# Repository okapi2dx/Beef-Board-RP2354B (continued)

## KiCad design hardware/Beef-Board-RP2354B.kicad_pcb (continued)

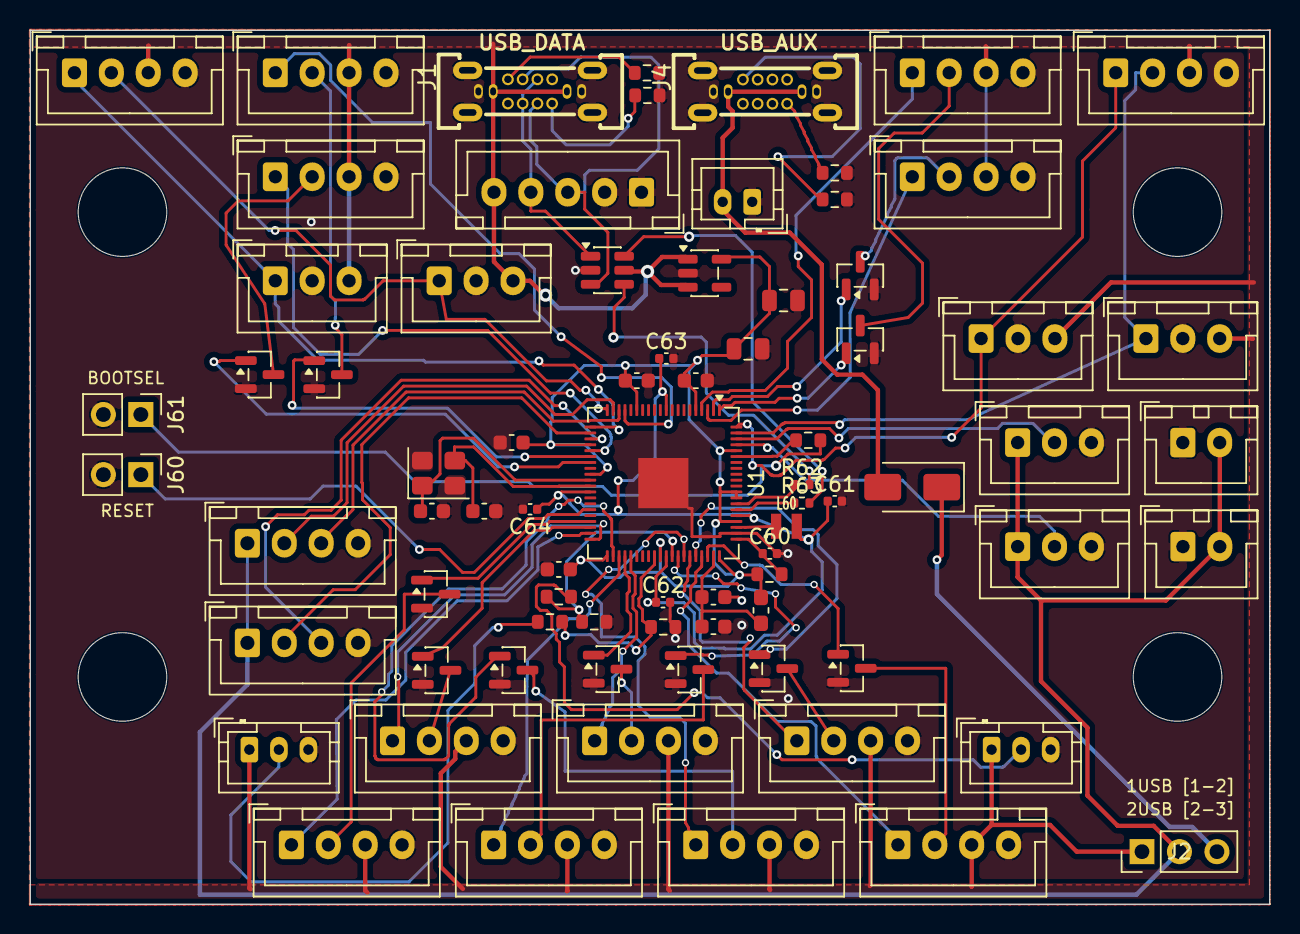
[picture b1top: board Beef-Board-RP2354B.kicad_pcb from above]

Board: 2 copper layers, 84.0 x 59.2 mm, 81 parts (0 on the bottom side), 72 nets.

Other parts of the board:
H1, H2, H3, H4: 6mm; MountingHole_6mm

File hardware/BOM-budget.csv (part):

Reference,Description/value,Qty,Footprint,Mounting,Suggested MPN (uncommitted),Manufacturer,LCSC SKU,Unit USD low,Unit USD high,Extended USD low,Extended USD high,Notes
C10,15pF,1,Capacitor_SMD:C_0603_1608Metric,SMT,0603 C0G/NP0 capacitor (candidate),Asian brands,,0.0050,0.0200,0.0050,0.0200,Capacitance per Value; voltage/tolerance not specified
C11,15pF,1,Capacitor_SMD:C_0603_1608Metric,SMT,0603 C0G/NP0 capacitor (candidate),Asian brands,,0.0050,0.0200,0.0050,0.0200,Capacitance per Value; voltage/tolerance not specified
C2,10uF,1,Capacitor_SMD:C_0805_2012Metric,SMT,0805 X5R/X7R capacitor (candidate),Asian brands,,0.0300,0.1000,0.0300,0.1000,10 uF; verify rated voltage and DC-bias derating
C3,4.7uF,1,Capacitor_SMD:C_0805_2012Metric,SMT,0805 X5R/X7R capacitor (candidate),Asian brands,,0.0200,0.0500,0.0200,0.0500,4.7 uF; verify rated voltage and DC-bias derating
C4,100nF,1,Capacitor_SMD:C_0603_1608Metric,SMT,"ceramic capacitor, X7R (candidate)",Asian brands,,0.0030,0.0150,0.0030,0.0150,Capacitance per Value; voltage/tolerance not specified
C5,100nF,1,Capacitor_SMD:C_0603_1608Metric,SMT,"ceramic capacitor, X7R (candidate)",Asian brands,,0.0030,0.0150,0.0030,0.0150,Capacitance per Value; voltage/tolerance not specified
C6,100nF,1,Capacitor_SMD:C_0603_1608Metric,SMT,"ceramic capacitor, X7R (candidate)",Asian brands,,0.0030,0.0150,0.0030,0.0150,Capacitance per Value; voltage/tolerance not specified
C60,4.7uF,1,Capacitor_SMD:C_0402_1005Metric,SMT,0402 X5R/X7R capacitor (candidate),Asian brands,,0.0100,0.0400,0.0100,0.0400,4.7 uF; verify rated voltage and DC-bias derating
C61,4.7uF,1,Capacitor_SMD:C_0402_1005Metric,SMT,0402 X5R/X7R capacitor (candidate),Asian brands,,0.0100,0.0400,0.0100,0.0400,4.7 uF; verify rated voltage and DC-bias derating
C62,100nF,1,Capacitor_SMD:C_0402_1005Metric,SMT,"ceramic capacitor, X7R (candidate)",Asian brands,,0.0030,0.0150,0.0030,0.0150,Capacitance per Value; voltage/tolerance not specified
C63,100nF,1,Capacitor_SMD:C_0402_1005Metric,SMT,"ceramic capacitor, X7R (candidate)",Asian brands,,0.0030,0.0150,0.0030,0.0150,Capacitance per Value; voltage/tolerance not specified
C64,100nF,1,Capacitor_SMD:C_0402_1005Metric,SMT,"ceramic capacitor, X7R (candidate)",Asian brands,,0.0030,0.0150,0.0030,0.0150,Capacitance per Value; voltage/tolerance not specified
C7,100nF,1,Capacitor_SMD:C_0603_1608Metric,SMT,"ceramic capacitor, X7R (candidate)",Asian brands,,0.0030,0.0150,0.0030,0.0150,Capacitance per Value; voltage/tolerance not specified
C8,1uF,1,Capacitor_SMD:C_0603_1608Metric,SMT,"ceramic capacitor, X7R (candidate)",Asian brands,,0.0030,0.0150,0.0030,0.0150,Capacitance per Value; voltage/tolerance not specified
C9,10nF,1,Capacitor_SMD:C_0603_1608Metric,SMT,"ceramic capacitor, X7R (candidate)",Asian brands,,0.0030,0.0150,0.0030,0.0150,Capacitance per Value; voltage/tolerance not specified
D1,SS34,1,Diode_SMD:D_SMA,SMT,SS34,generic,,0.0700,0.1300,0.0700,0.1300,SMA Schottky; verify voltage/current requirements
FB1,600R@100MHz,1,Inductor_SMD:L_0603_1608Metric_Pad1.05x0.95mm_HandSolder,SMT,BLM18AG601SN1 or equivalent,Murata/equivalent,,0.0300,0.0800,0.0300,0.0800,"0603 ferrite, 600 ohm @ 100 MHz; candidate only"
J1,USB-C DEVICE,1,BEEF-BOARD:USB-C-TH_G-SWITCH_GT-USB-7038X_1,THT,GT-USB-7038X (verify exact mechanical variant),G-Switch,,,,,,PCB footprint matches GT-USB-7038X family; verify exact body height/length against the selected part before purchase; previous SKU and price were for a different connector
J10,VAUX OUT,1,Connector_JST:JST_XH_B2B-XH-A_1x02_P2.50mm_Vertical,THT,B2B-XH-A(LF)(SN),JST,C158012,0.0408,0.0700,0.0408,0.0700,LCSC price tier; THT
J11,B1 LEGACY,1,Connector_JST:JST_XH_B4B-XH-A_1x04_P2.50mm_Vertical,THT,B4B-XH-A(LF)(SN),JST,C144395,0.0373,0.0700,0.0373,0.0700,LCSC price tier; THT
J12,B2 LEGACY,1,Connector_JST:JST_XH_B4B-XH-A_1x04_P2.50mm_Vertical,THT,B4B-XH-A(LF)(SN),JST,C144395,0.0373,0.0700,0.0373,0.0700,LCSC price tier; THT
J13,B3 LEGACY,1,Connector_JST:JST_XH_B4B-XH-A_1x04_P2.50mm_Vertical,THT,B4B-XH-A(LF)(SN),JST,C144395,0.0373,0.0700,0.0373,0.0700,LCSC price tier; THT
J14,B4 LEGACY,1,Connector_JST:JST_XH_B4B-XH-A_1x04_P2.50mm_Vertical,THT,B4B-XH-A(LF)(SN),JST,C144395,0.0373,0.0700,0.0373,0.0700,LCSC price tier; THT
J15,B5 LEGACY,1,Connector_JST:JST_XH_B4B-XH-A_1x04_P2.50mm_Vertical,THT,B4B-XH-A(LF)(SN),JST,C144395,0.0373,0.0700,0.0373,0.0700,LCSC price tier; THT
J16,B6 LEGACY,1,Connector_JST:JST_XH_B4B-XH-A_1x04_P2.50mm_Vertical,THT,B4B-XH-A(LF)(SN),JST,C144395,0.0373,0.0700,0.0373,0.0700,LCSC price tier; THT
J17,B7 LEGACY,1,Connector_JST:JST_XH_B4B-XH-A_1x04_P2.50mm_Vertical,THT,B4B-XH-A(LF)(SN),JST,C144395,0.0373,0.0700,0.0373,0.0700,LCSC price tier; THT
J18,B8 LEGACY,1,Connector_JST:JST_XH_B4B-XH-A_1x04_P2.50mm_Vertical,THT,B4B-XH-A(LF)(SN),JST,C144395,0.0373,0.0700,0.0373,0.0700,LCSC price tier; THT
J19,B9 LEGACY,1,Connector_JST:JST_XH_B4B-XH-A_1x04_P2.50mm_Vertical,THT,B4B-XH-A(LF)(SN),JST,C144395,0.0373,0.0700,0.0373,0.0700,LCSC price tier; THT
J2,POWER SELECT,1,Connector_PinHeader_2.54mm:PinHeader_1x03_P2.54mm_Vertical,"THT, front side",,,,,,,,"Add a 2.54 mm shunt. Pins 1-2 short: J1 only. Pins 2-3 short: J1 plus J4, with J4 power through D1. Select header and shunt rated for the load current."
J20,B10 LEGACY,1,Connector_JST:JST_XH_B4B-XH-A_1x04_P2.50mm_Vertical,THT,B4B-XH-A(LF)(SN),JST,C144395,0.0373,0.0700,0.0373,0.0700,LCSC price tier; THT
J21,B11 LEGACY,1,Connector_JST:JST_XH_B4B-XH-A_1x04_P2.50mm_Vertical,THT,B4B-XH-A(LF)(SN),JST,C144395,0.0373,0.0700,0.0373,0.0700,LCSC price tier; THT
J22,USB COMMON,1,Connector_JST:JST_XH_B5B-XH-A_1x05_P2.50mm_Vertical,THT,B5B-XH-A(LF)(SN),JST,C157991,0.0473,0.1500,0.0473,0.1500,LCSC reference price; THT
J3,VAUX 5V INPUT,1,"TerminalBlock_Phoenix:TerminalBlock_Phoenix_MKDS-1,5-2_1x02_P5.00mm_Horizontal",THT,KF301-5.0-2P (candidate; verify footprint),generic terminal block,C474881,0.3000,1.0000,0.3000,1.0000,5.00 mm 2-pin price allowance; footprint match required; pin 1 GND, pin 2 EXT_5V
J31,ENCODER 1,1,Connector_JST:JST_XH_B4B-XH-A_1x04_P2.50mm_Vertical,THT,B4B-XH-A(LF)(SN),JST,C144395,0.0373,0.0700,0.0373,0.0700,LCSC price tier; THT
J32,ENCODER 2,1,Connector_JST:JST_XH_B4B-XH-A_1x04_P2.50mm_Vertical,THT,B4B-XH-A(LF)(SN),JST,C144395,0.0373,0.0700,0.0373,0.0700,LCSC price tier; THT
J33,AE1 0-5V,1,Connector_JST:JST_XH_B3B-XH-A_1x03_P2.50mm_Vertical,THT,B3B-XH-A(LF)(SN),JST,C144394,0.0332,0.1000,0.0332,0.1000,LCSC reference price; THT
J34,AE2 0-5V,1,Connector_JST:JST_XH_B3B-XH-A_1x03_P2.50mm_Vertical,THT,B3B-XH-A(LF)(SN),JST,C144394,0.0332,0.1000,0.0332,0.1000,LCSC reference price; THT
J4,USB-C AUX POWER,1,BEEF-BOARD:USB-C-TH_G-SWITCH_GT-USB-7038X_1,THT,GT-USB-7038X (verify exact mechanical variant),G-Switch,,,,,,PCB footprint matches GT-USB-7038X family; verify exact body height/length against the selected part before purchase; previous SKU and price were for a different connector
J40,TT RGB,1,Connector_JST:JST_XH_B3B-XH-A_1x03_P2.50mm_Vertical,THT,B3B-XH-A(LF)(SN),JST,C144394,0.0332,0.1000,0.0332,0.1000,LCSC reference price; THT
J41,CENTER BAR RGB,1,Connector_JST:JST_XH_B3B-XH-A_1x03_P2.50mm_Vertical,THT,B3B-XH-A(LF)(SN),JST,C144394,0.0332,0.1000,0.0332,0.1000,LCSC reference price; THT
J42,UART A 3V3,1,Connector_JST:JST_XH_B4B-XH-A_1x04_P2.50mm_Vertical,THT,B4B-XH-A(LF)(SN),JST,C144395,0.0373,0.0700,0.0373,0.0700,LCSC price tier; THT
J43,UART B 3V3,1,Connector_JST:JST_XH_B4B-XH-A_1x04_P2.50mm_Vertical,THT,B4B-XH-A(LF)(SN),JST,C144395,0.0373,0.0700,0.0373,0.0700,LCSC price tier; THT
J5,ENC1 A,1,Connector_JST:JST_XH_B3B-XH-A_1x03_P2.50mm_Vertical,THT,B3B-XH-A(LF)(SN),JST,C144394,0.0332,0.1000,0.0332,0.1000,LCSC reference price; THT
J6,ENC1 B,1,Connector_JST:JST_XH_B3B-XH-A_1x03_P2.50mm_Vertical,THT,B3B-XH-A(LF)(SN),JST,C144394,0.0332,0.1000,0.0332,0.1000,LCSC reference price; THT
J60,RESET HEADER,1,Connector_PinHeader_2.54mm:PinHeader_1x02_P2.54mm_Vertical,THT,,,,0.0000,0.0000,0.0000,0.0000,Needs exact orderable part selection
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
